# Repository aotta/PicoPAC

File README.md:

# PicoPAC v.1.0b
Flashcart for Videopac / Odyssey 2 based on Wilco2009 Videopac-microSD card project
Based on SD card by Wilco2009: https://github.com/wilco2009/Videopac-micro-SD-Cart , my greetings for his fantastic job!

Since now, tested on  G-7000, G7400, C52, JOPAC and Odyssey 2. Waiting for a friend that has to repair his G7200 for completing the list ;) 

--changelog v.1.0a ->
Added support to extROM games too (VP_40 and VP_31).
Added filename reading from flash (max files read = 25*8) 

--changelog v.1.0b ->
fixed KTAA final rom

Other info also on Nightfallcrew blog: https://www.nightfallcrew.com/22/09/2024/flash-multicart-for-philips-videopac-magnavox-odyssey-2/

PicoPAC is a multicart DIY yourself based on cheap "PURPLE" Raspberry Pi Pico clone, easy to build and not expensive.
**WARNING!** "purple" Pico has not the same pinout of original Raspberry "green" ones, you MUST use the clone or you may damage your hardware.

**NOTE** You should find all the ROM following this site https://rene-g7400.datatex.nl/ 
Please don't forget to upload the here provided "selectgame.bin" and "selectgame.$$$" file in flash!!!!
Also, even if now you can change filenames, remember that extROM games are checked by name, so they works only if named "VP_31.bin", "VP_40.bin" or "4inarow.bin"!

**NOTE 2** 3D files for shell are WIP and probably the PCB doesn't fit perfectly withous some cut/drill to PCB holes!! (Thanks to Mike Wilson for the Logo version)

Added alternate STLs files thanks to kokkiklhs (see https://forums.atariage.com/topic/370606-picopac-a-pico-purple-porting-of-videopac-microsdcard/page/4/#comment-5700299 for further details)

Kicad project and gerbers files for the pcb are in the PCB folder, you need only a diode and a push buttons for resetting the cart if needed or want restart. 
Add you pico clone, and flash the firmware ".uf2" in the Pico by connecting it while pressing button on Pico and drop it in the opened windows on PC.
After flashed with firmware, and every time you have to change your ROMS repository, you can simply connect the Pico to PC and drag&drop "BIN" files  into.
But remember that only games already in menu will be seen by the cart.

Even if the diode should protect your console, **DO NOT CONNECT PICO WHILE INSERTED IN A POWERED ON CONSOLE!**

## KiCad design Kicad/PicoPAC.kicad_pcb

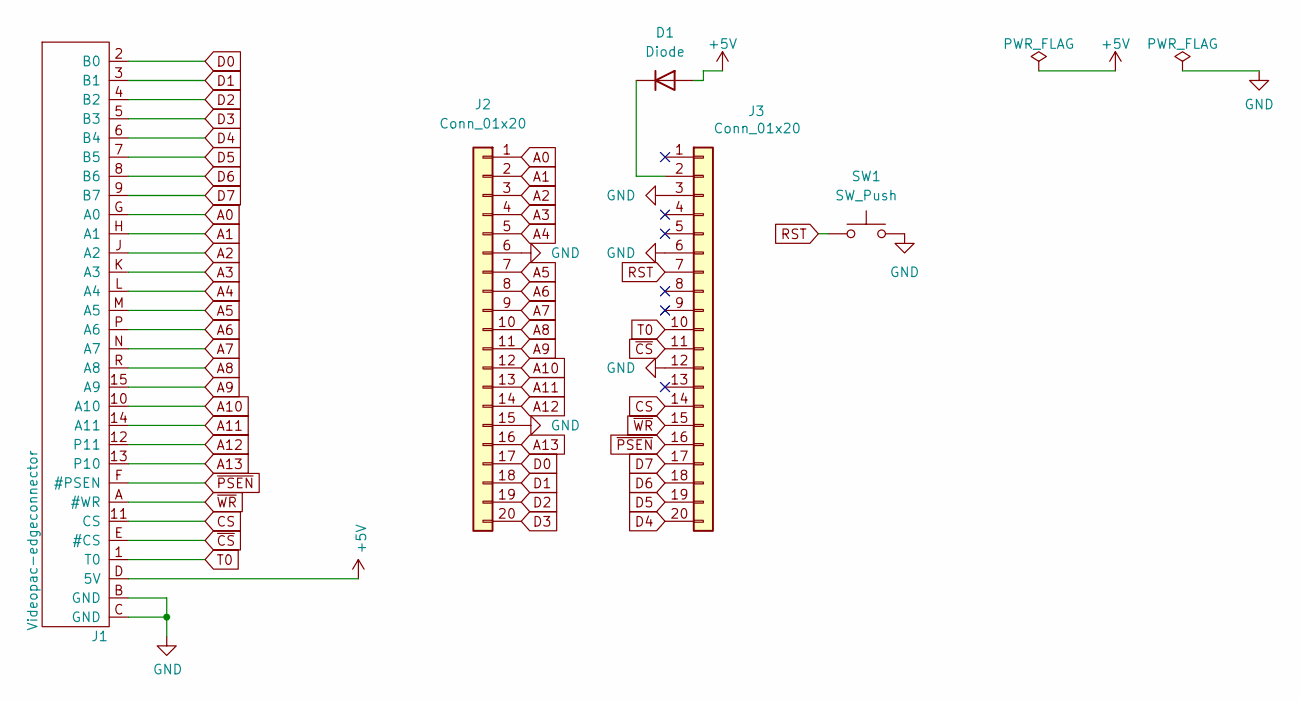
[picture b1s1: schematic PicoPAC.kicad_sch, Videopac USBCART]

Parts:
D1: Diode; D_DO-35_SOD27_P7.62mm_Horizontal
J1: Videopac-edgeconnector; videopac-edgecon
J2, J3: Conn_01x20; PinSocket_1x20_P2.54mm_Vertical
SW1: SW_Push; SW_PUSH_6mm

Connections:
+5V: D1.2 (A), J1.D (5V)
A0: J1.G (A0), J2.1
A1: J1.H (A1), J2.2
A2: J1.J (A2), J2.3
A3: J1.K (A3), J2.4
A4: J1.L (A4), J2.5
A5: J1.M (A5), J2.7
A6: J1.P (A6), J2.8
A7: J1.N (A7), J2.9
A8: J1.R (A8), J2.10
A9: J1.15 (A9), J2.11
A10: J1.10 (A10), J2.12
A11: J1.14 (A11), J2.13
A12: J1.12 (P11), J2.14
A13: J1.13 (P10), J2.16
CS: J1.11 (CS), J3.14
D0: J1.2 (B0), J2.17
D1: J1.3 (B1), J2.18
D2: J1.4 (B2), J2.19
D3: J1.5 (B3), J2.20
D4: J1.6 (B4), J3.20
D5: J1.7 (B5), J3.19
D6: J1.8 (B6), J3.18
D7: J1.9 (B7), J3.17
GND: J1.B (GND), J1.C (GND), J2.6, J2.15, J3.3, J3.6, J3.12, SW1.2
unnamed: D1.1 (K), J3.2
RST: J3.7, SW1.1
T0: J1.1 (T0), J3.10
~CS: J1.E (#CS), J3.11
~PSEN: J1.F (#PSEN), J3.16
~WR: J1.A (#WR), J3.15

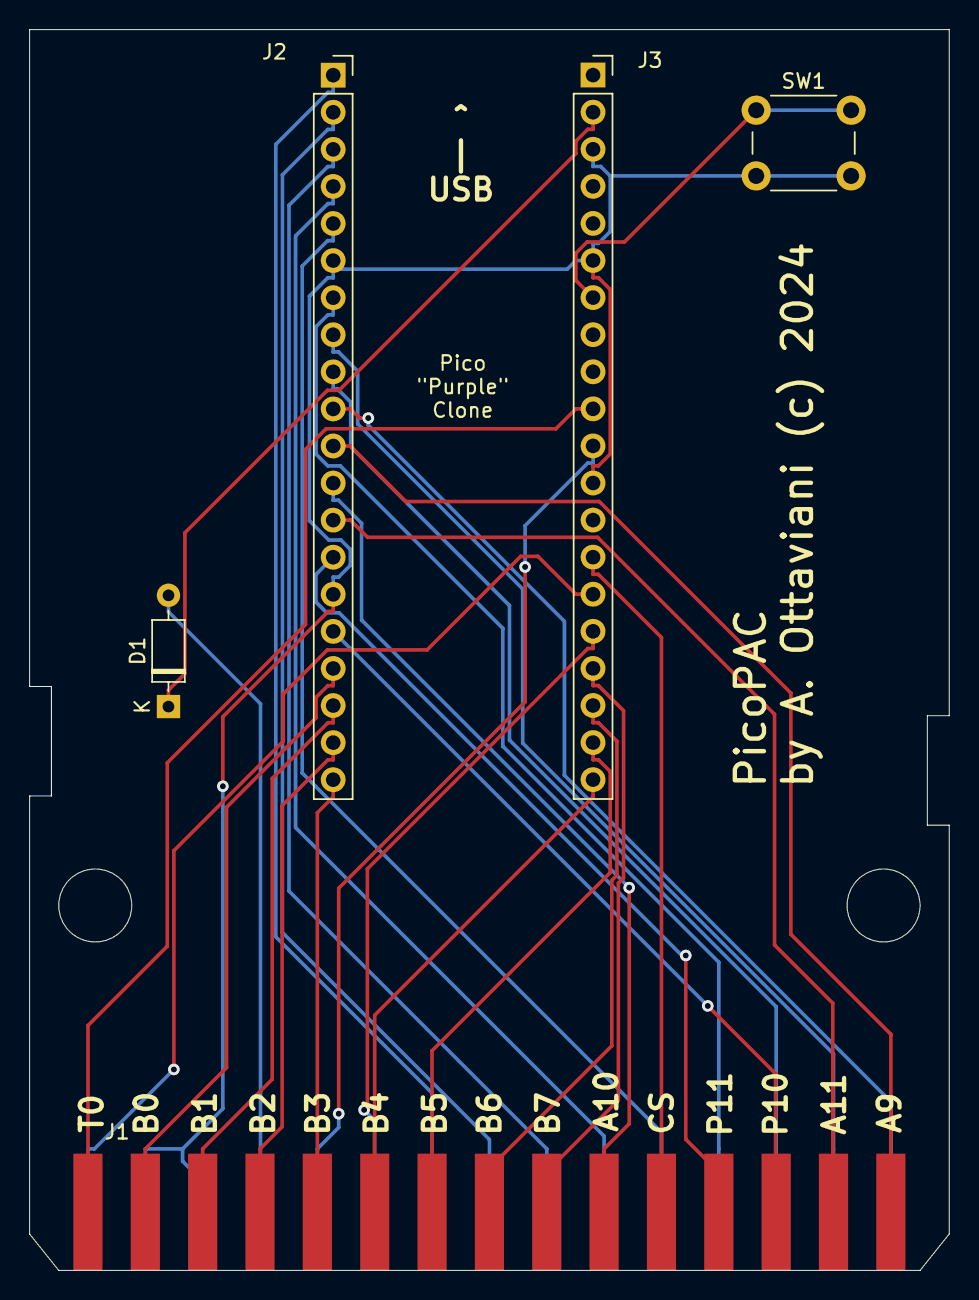
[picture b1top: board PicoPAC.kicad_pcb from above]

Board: 2 copper layers, 63.0 x 85.0 mm, 5 parts (0 on the bottom side), 31 nets.

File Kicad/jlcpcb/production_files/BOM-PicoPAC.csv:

Comment,Designator,Footprint,LCSC
Conn_01x20,J3,PinSocket_1x20_P2.54mm_Vertical,
Conn_01x20,J2,PinSocket_1x20_P2.54mm_Vertical,
SW_Push,SW1,SW_PUSH_6mm,
Diode ,D1,D_DO-35_SOD27_P7.62mm_Horizontal,
Videopac-edgeconnector,J1,videopac-edgecon,

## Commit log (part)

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2024-09-03 Delete VSC-PicoPAC/filelist.h
    duplicated file, not needed
2024-09-05 Add files via upload
    New version compatible with G-7000
2024-09-05 Rename selectgame.bin to selectgame.bin.old
2024-09-05 Add files via upload
    Fixed VP31 & VP40 carts
2024-09-05 Update README.md
    added info about compatibility and fix for exROM games
2024-09-05 Add files via upload
    new version with fixed ram location for G-7000 compatibility
2024-09-05 Add files via upload
    fixed ram location for G-7000 compatibility, added exROM (game VP31 e VP40) support
2024-09-09 Update README.md
    added note for 3d stl files
2024-09-11 Add files via upload
    Version 1.0a with file manager
2024-09-11 Update README.md
    updatet to v. 1.0a with file manager
2024-09-11 Add files via upload
    update to ver. 1.0a
2024-09-11 Add files via upload
    a couple of tracks moved
2024-09-25 Delete VSC-PicoPAC/gamelist.h
    no more needed in 1.0a
2024-10-28 Delete 3dPrint/Shell PirtoII Eskimo version directory
    wrong repo
2025-03-28 updated to v.1.0b
    fixed KTAA rom
2025-03-28 new 1.0b version
    fixed KTAA final rom
2025-07-26 Add files via upload
    moved a little the pillars to better fitting
2025-07-26 Add files via upload
    little move to pillars for better fitting
2025-08-11 Add files via upload
    Alternate shell by Kokkiklhs
2025-08-11 Update README.md
    added alternate stls files

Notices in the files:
Kicad/PicoPAC.kicad_pcb:
by A. Ottaviani (c) 2024
